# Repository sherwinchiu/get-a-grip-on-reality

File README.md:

# get-a-grip-on-reality
fydp project 2025 for vr gloves. open source pcb

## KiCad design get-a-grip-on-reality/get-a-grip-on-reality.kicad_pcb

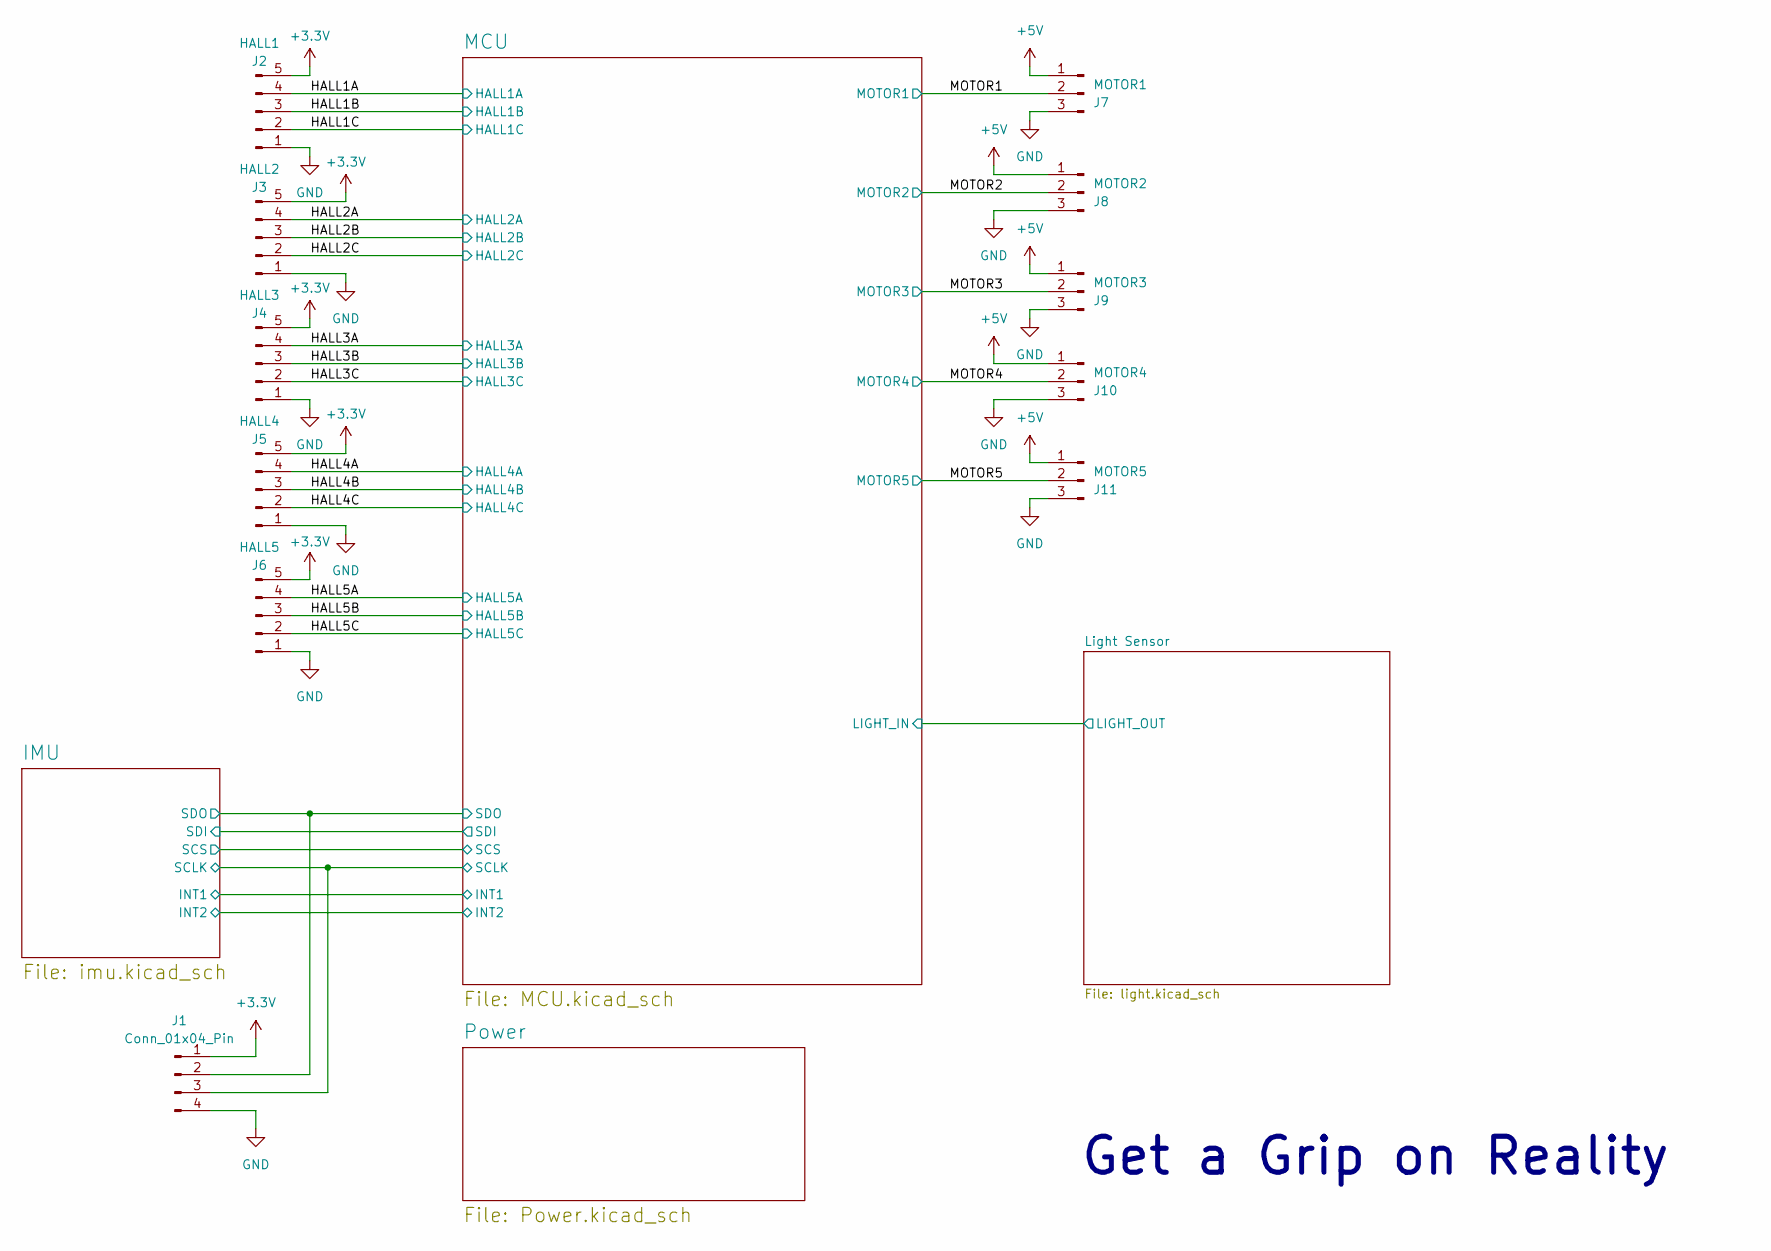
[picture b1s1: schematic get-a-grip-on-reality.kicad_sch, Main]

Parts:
J1: Conn_01x04_Pin; PinHeader_1x04_P2.54mm_Vertical
J2: HALL1; JST_SH_BM05B-SRSS-TB_1x05-1MP_P1.00mm_Vertical
J3: HALL2; JST_SH_BM05B-SRSS-TB_1x05-1MP_P1.00mm_Vertical
J4: HALL3; JST_SH_BM05B-SRSS-TB_1x05-1MP_P1.00mm_Vertical
J5: HALL4; JST_SH_BM05B-SRSS-TB_1x05-1MP_P1.00mm_Vertical
J6: HALL5; JST_SH_BM05B-SRSS-TB_1x05-1MP_P1.00mm_Vertical
J7: MOTOR1; PinHeader_1x03_P2.54mm_Vertical
J8: MOTOR2; PinHeader_1x03_P2.54mm_Vertical
J9: MOTOR3; PinHeader_1x03_P2.54mm_Vertical
J10: MOTOR4; PinHeader_1x03_P2.54mm_Vertical
J11: MOTOR5; PinHeader_1x03_P2.54mm_Vertical

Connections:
+3.3V: J1.1, J2.5, J3.5, J4.5, J5.5, J6.5; also elsewhere on the board
+5V: J7.1, J8.1, J9.1, J10.1, J11.1; also elsewhere on the board
/HALL1A: J2.4; also elsewhere on the board
/HALL1B: J2.3; also elsewhere on the board
/HALL1C: J2.2; also elsewhere on the board
/HALL2A: J3.4; also elsewhere on the board
/HALL2B: J3.3; also elsewhere on the board
/HALL2C: J3.2; also elsewhere on the board
/HALL3A: J4.4; also elsewhere on the board
/HALL3B: J4.3; also elsewhere on the board
/HALL3C: J4.2; also elsewhere on the board
/HALL4A: J5.4; also elsewhere on the board
/HALL4B: J5.3; also elsewhere on the board
/HALL4C: J5.2; also elsewhere on the board
/HALL5A: J6.4; also elsewhere on the board
/HALL5B: J6.3; also elsewhere on the board
/HALL5C: J6.2; also elsewhere on the board
/IMU/SCLK: J1.3; also elsewhere on the board
/IMU/SDO: J1.2; also elsewhere on the board
/MOTOR1: J7.2; also elsewhere on the board
/MOTOR2: J8.2; also elsewhere on the board
/MOTOR3: J9.2; also elsewhere on the board
/MOTOR4: J10.2; also elsewhere on the board
/MOTOR5: J11.2; also elsewhere on the board
GND: J1.4, J2.1, J3.1, J4.1, J5.1, J6.1, J7.3, J8.3, J9.3, J10.3, J11.3; also elsewhere on the board

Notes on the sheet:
Get a Grip on Reality

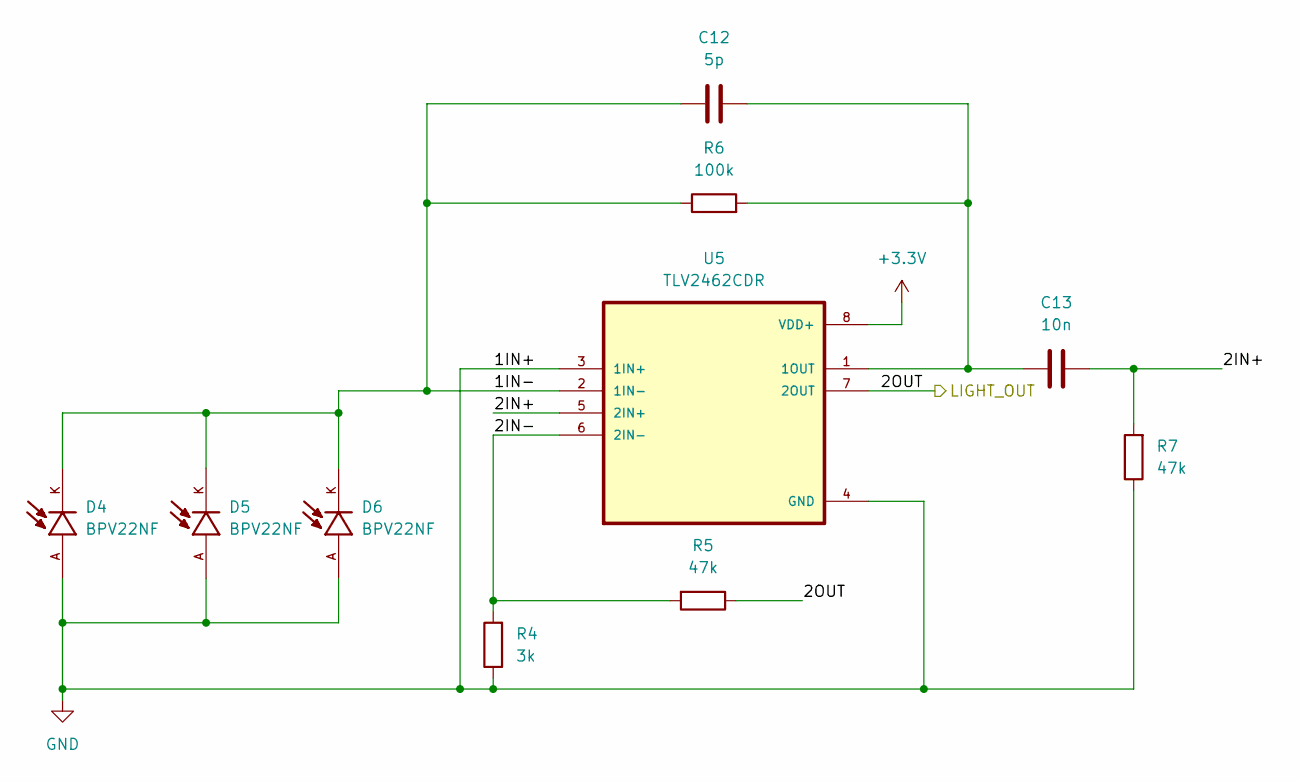
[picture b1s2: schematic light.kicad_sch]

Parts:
C12: 5p; C_0805_2012Metric
C13: 10n; C_0805_2012Metric
D4, D5, D6: BPV22NF; XDCR_BPV22NF; PARTREV 1.9
R4: 3k; R_0805_2012Metric
R5, R7: 47k; R_0805_2012Metric
R6: 100k; R_0805_2012Metric
U5: TLV2462CDR; SOIC127P599X175-8N

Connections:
+3.3V: U5.8 (VDD+); also elsewhere on the board
/Light Sensor/1IN-: C12.1, D4.K, D5.K, D6.K, R6.1, U5.2 (1IN-)
/Light Sensor/2IN+: C13.2, R7.2, U5.5 (2IN+)
/Light Sensor/2IN-: R4.2, R5.2, U5.6 (2IN-)
/Light Sensor/2OUT: R5.1, U5.7 (2OUT); also elsewhere on the board
GND: D4.A, D5.A, D6.A, R4.1, R7.1, U5.3 (1IN+), U5.4 (GND); also elsewhere on the board
unnamed: C12.2, C13.1, R6.2, U5.1 (1OUT)

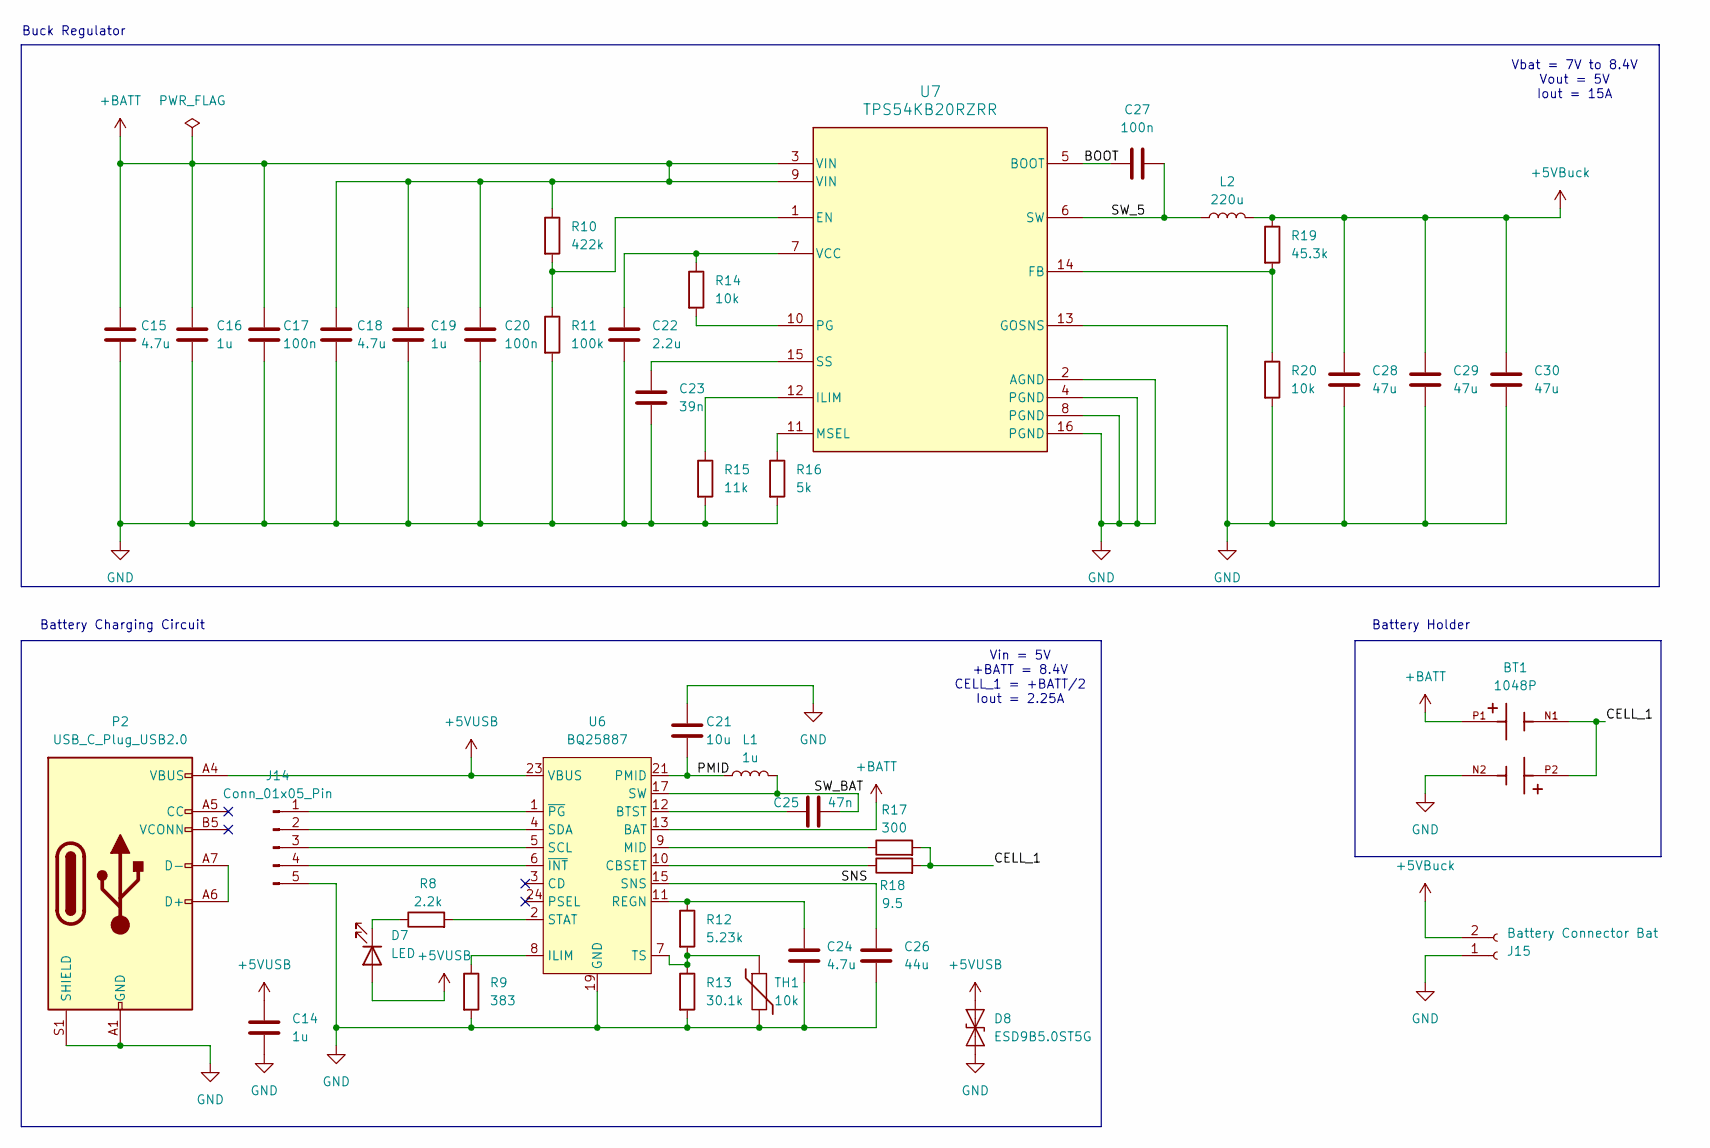
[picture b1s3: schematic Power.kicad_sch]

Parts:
BT1: 1048P; BAT_1048P; PARTREV A
C14, C16, C19: 1u; C_0805_2012Metric
C15, C18, C24: 4.7u; C_0805_2012Metric
C17, C20, C27: 100n; C_0805_2012Metric
C21: 10u; C_0805_2012Metric
C22: 2.2u; C_0805_2012Metric
C23: 39n; C_0805_2012Metric
C25: 47n; C_0805_2012Metric
C26: 44u; C_0805_2012Metric
C28, C29, C30: 47u; C_0805_2012Metric
D7: LED; LED_0805_2012Metric
D8: ESD9B5.0ST5G; D_SOD-923
J14: Conn_01x05_Pin; PinHeader_1x05_P2.54mm_Vertical
J15: Battery Connector Bat; AMASS_XT30PW-F_1x02_P2.50mm_Horizontal
L1: 1u; L_Taiyo-Yuden_MD-2020
L2: 220u; L_Bourns_SRU5016_5.2x5.2mm
P2: USB_C_Plug_USB2.0; USB_C_Receptacle_GCT_USB4110
R8: 2.2k; R_0805_2012Metric
R9: 383; R_0805_2012Metric
R10: 422k; R_0805_2012Metric
R11: 100k; R_0805_2012Metric
R12: 5.23k; R_0805_2012Metric
R13: 30.1k; R_0805_2012Metric
R14, R20: 10k; R_0805_2012Metric
R15: 11k; R_0805_2012Metric
R16: 5k; R_0805_2012Metric
R17: 300; R_0805_2012Metric
R18: 9.5; R_0805_2012Metric
R19: 45.3k; R_0805_2012Metric
TH1: 10k; R_0805_2012Metric
U6: BQ25887; VQFN-24-1EP_4x4mm_P0.5mm_EP2.5x2.5mm
U7: TPS54KB20RZRR; RZR0016A-MFG

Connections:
+5VBuck: C28.1, C29.1, C30.1, J15.2, L2.2, R19.1
+5VUSB: C14.1, D7.2 (A), D8.2 (A2), P2.A4 (VBUS), P2.A9 (VBUS), P2.B4 (VBUS), P2.B9 (VBUS), U6.23 (VBUS)
+BATT: BT1.P1, C15.1, C16.1, C17.1, C18.1, C19.1, C20.1, R10.1, U6.13 (BAT), U6.14 (BAT), U7.3 (VIN), U7.9 (VIN)
/Power/BOOT: C27.1, U7.5 (BOOT)
/Power/CELL_1: BT1.N1, BT1.P2, R17.2, R18.2
/Power/PMID: C21.2, L1.1, U6.21 (PMID), U6.22 (PMID)
/Power/SNS: C26.1, U6.15 (SNS), U6.16 (SNS)
/Power/SW_5: C27.2, L2.1, U7.6 (SW)
/Power/SW_BAT: C25.2, L1.2, U6.17 (SW), U6.18 (SW)
GND: BT1.N2, C14.2, C15.2, C16.2, C17.2, C18.2, C19.2, C20.2, C21.1, C22.2, C23.2, C24.2, C26.2, C28.2, C29.2, C30.2, D8.1 (A1), J14.5, J15.1, P2.A1 (GND), P2.A12 (GND), P2.B1 (GND), P2.B12 (GND), P2.S1 (SHIELD), R9.2, R11.2, R13.2, R15.2, R16.2, R20.2, TH1.2, U6.19 (GND), U6.20 (GND), U7.2 (AGND), U7.4 (PGND), U7.8 (PGND), U7.13 (GOSNS), U7.16 (PGND); also elsewhere on the board
unnamed: D7.1 (K), R8.1
unnamed: J14.1, U6.1 (~PG)
unnamed: J14.2, U6.4 (SDA)
unnamed: J14.3, U6.5 (SCL)
unnamed: J14.4, U6.6 (~INT)
unnamed: P2.A6 (D+), P2.A7 (D-)
unnamed: C25.1, U6.12 (BTST)
unnamed: R18.1, U6.10 (CBSET)
unnamed: R9.1, U6.8 (ILIM)
unnamed: R17.1, U6.9 (MID)
unnamed: C24.1, R12.1, U6.11 (REGN)
unnamed: R8.2, U6.2 (STAT)
unnamed: R12.2, R13.1, TH1.1, U6.7 (TS)
unnamed: R10.2, R11.1, U7.1 (EN)
unnamed: R19.2, R20.1, U7.14 (FB)
unnamed: R15.1, U7.12 (ILIM)
unnamed: R16.1, U7.11 (MSEL)
unnamed: R14.2, U7.10 (PG)
unnamed: C23.1, U7.15 (SS)
unnamed: C22.1, R14.1, U7.7 (VCC)

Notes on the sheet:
Vbat = 7V to 8.4V Vout = 5V Iout = 15A
Buck Regulator
Vin = 5V +BATT = 8.4V CELL_1 = +BATT/2 Iout = 2.25A
Battery Charging Circuit
Battery Holder

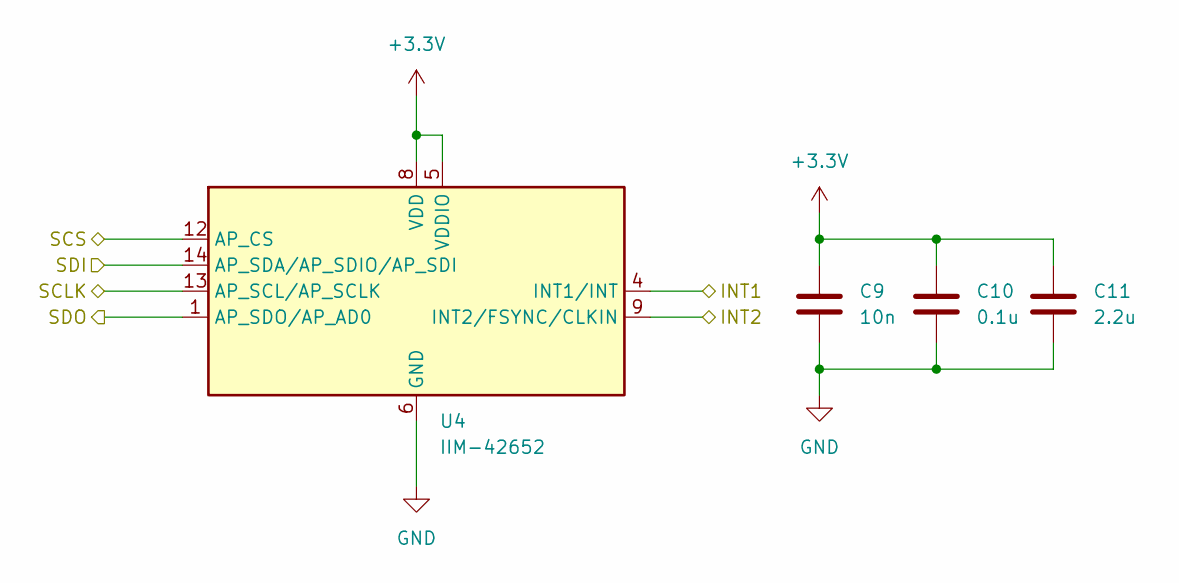
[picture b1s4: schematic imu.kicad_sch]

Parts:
C9: 10n; C_0805_2012Metric
C10: 0.1u; C_0805_2012Metric
C11: 2.2u; C_0805_2012Metric
U4: IIM-42652; Bosch_LGA-14_3x2.5mm_P0.5mm

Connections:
+3.3V: C9.1, C10.1, C11.1, U4.5 (VDDIO), U4.8 (VDD); also elsewhere on the board
/IMU/INT1: U4.4 (INT1/INT); also elsewhere on the board
/IMU/INT2: U4.9 (INT2/FSYNC/CLKIN); also elsewhere on the board
/IMU/SCLK: U4.13 (AP_SCL/AP_SCLK); also elsewhere on the board
/IMU/SCS: U4.12 (AP_CS); also elsewhere on the board
/IMU/SDI: U4.14 (AP_SDA/AP_SDIO/AP_SDI); also elsewhere on the board
/IMU/SDO: U4.1 (AP_SDO/AP_AD0); also elsewhere on the board
GND: C9.2, C10.2, C11.2, U4.6 (GND), U4.7 (GND); also elsewhere on the board

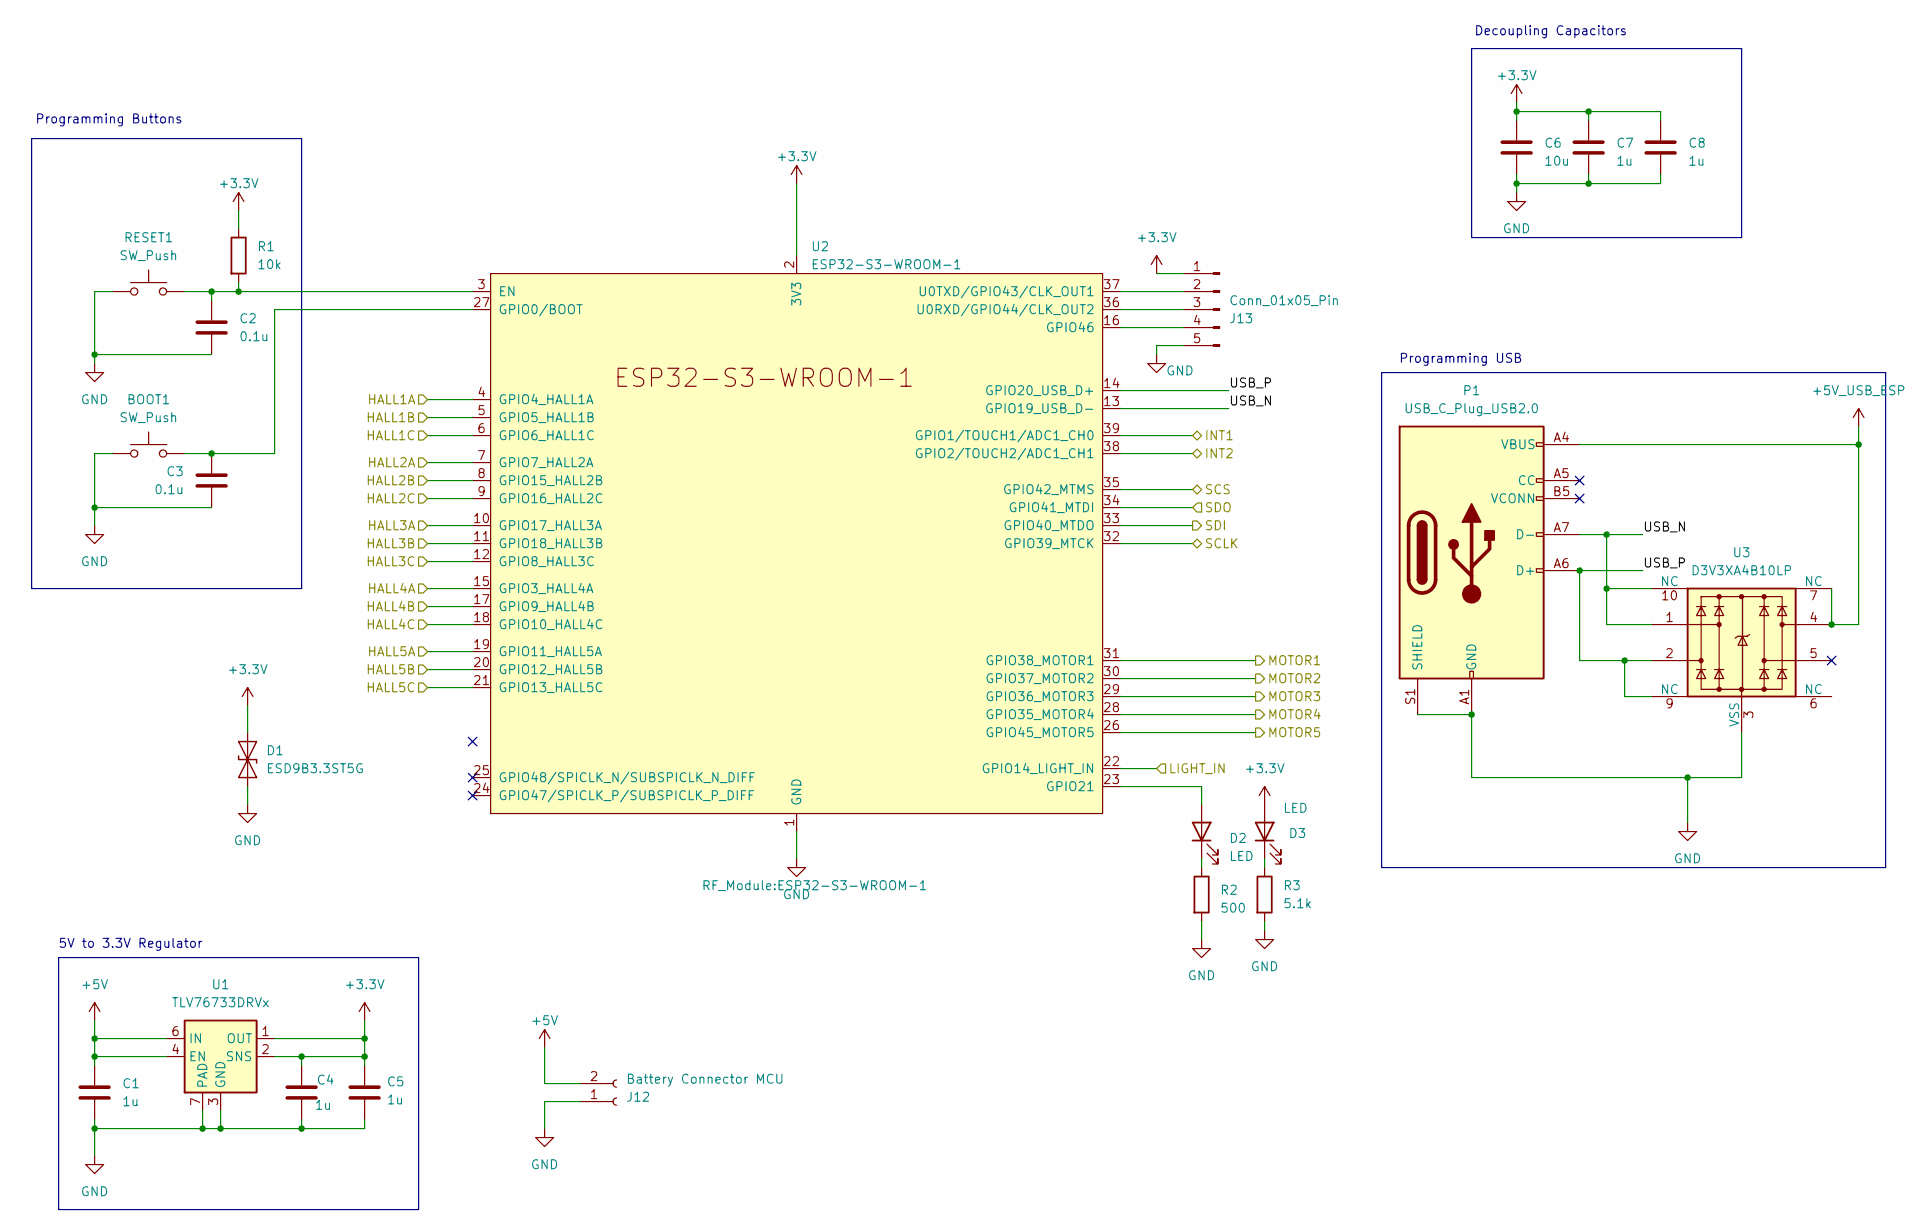
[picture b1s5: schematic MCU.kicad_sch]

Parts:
BOOT1: SW_Push; SW_SPST_EVPBF
C1, C4, C5, C7, C8: 1u; C_0805_2012Metric
C2, C3: 0.1u; C_0805_2012Metric
C6: 10u; C_0805_2012Metric
D1: ESD9B3.3ST5G; D_SOD-923
D2, D3: LED; LED_0805_2012Metric
J12: Battery Connector MCU; AMASS_XT30PW-M_1x02_P2.50mm_Horizontal
J13: Conn_01x05_Pin; PinHeader_1x05_P2.54mm_Vertical
P1: USB_C_Plug_USB2.0; USB_C_Receptacle_GCT_USB4110
R1: 10k; R_0805_2012Metric
R2: 500; R_0805_2012Metric
R3: 5.1k; R_0805_2012Metric
RESET1: SW_Push; SW_SPST_EVPBF
U1: TLV76733DRVx; WSON-6-1EP_2x2mm_P0.65mm_EP1x1.6mm_ThermalVias
U2: ESP32-S3-WROOM-1
U3: D3V3XA4B10LP; Diodes_UDFN-10_1.0x2.5mm_P0.5mm

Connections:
+3.3V: C4.1, C5.1, C6.1, C7.1, C8.1, D1.2 (A2), D3.2 (A), J13.1, R1.1, U1.1 (OUT), U1.2 (SNS), U2.2 (3V3); also elsewhere on the board
+5V: C1.1, J12.2, U1.4 (EN), U1.6 (IN); also elsewhere on the board
+5V_USB_ESP: P1.A4 (VBUS), P1.A9 (VBUS), P1.B4 (VBUS), P1.B9 (VBUS), U3.4, U3.7 (NC)
/HALL1A: U2.4 (GPIO4_HALL1A); also elsewhere on the board
/HALL1B: U2.5 (GPIO5_HALL1B); also elsewhere on the board
/HALL1C: U2.6 (GPIO6_HALL1C); also elsewhere on the board
/HALL2A: U2.7 (GPIO7_HALL2A); also elsewhere on the board
/HALL2B: U2.8 (GPIO15_HALL2B); also elsewhere on the board
/HALL2C: U2.9 (GPIO16_HALL2C); also elsewhere on the board
/HALL3A: U2.10 (GPIO17_HALL3A); also elsewhere on the board
/HALL3B: U2.11 (GPIO18_HALL3B); also elsewhere on the board
/HALL3C: U2.12 (GPIO8_HALL3C); also elsewhere on the board
/HALL4A: U2.15 (GPIO3_HALL4A); also elsewhere on the board
/HALL4B: U2.17 (GPIO9_HALL4B); also elsewhere on the board
/HALL4C: U2.18 (GPIO10_HALL4C); also elsewhere on the board
/HALL5A: U2.19 (GPIO11_HALL5A); also elsewhere on the board
/HALL5B: U2.20 (GPIO12_HALL5B); also elsewhere on the board
/HALL5C: U2.21 (GPIO13_HALL5C); also elsewhere on the board
/IMU/INT1: U2.39 (GPIO1/TOUCH1/ADC1_CH0); also elsewhere on the board
/IMU/INT2: U2.38 (GPIO2/TOUCH2/ADC1_CH1); also elsewhere on the board
/IMU/SCLK: U2.32 (GPIO39_MTCK); also elsewhere on the board
/IMU/SCS: U2.35 (GPIO42_MTMS); also elsewhere on the board
/IMU/SDI: U2.33 (GPIO40_MTDO); also elsewhere on the board
/IMU/SDO: U2.34 (GPIO41_MTDI); also elsewhere on the board
/Light Sensor/2OUT: U2.22 (GPIO14_LIGHT_IN); also elsewhere on the board
/MCU/USB_N: P1.A7 (D-), U2.13 (GPIO19_USB_D-), U3.1, U3.10 (NC)
/MCU/USB_P: P1.A6 (D+), U2.14 (GPIO20_USB_D+), U3.2, U3.9 (NC)
/MOTOR1: U2.31 (GPIO38_MOTOR1); also elsewhere on the board
/MOTOR2: U2.30 (GPIO37_MOTOR2); also elsewhere on the board
/MOTOR3: U2.29 (GPIO36_MOTOR3); also elsewhere on the board
/MOTOR4: U2.28 (GPIO35_MOTOR4); also elsewhere on the board
/MOTOR5: U2.26 (GPIO45_MOTOR5); also elsewhere on the board
GND: BOOT1.2, C1.2, C2.2, C3.2, C4.2, C5.2, C6.2, C7.2, C8.2, D1.1 (A1), J12.1, J13.5, P1.A1 (GND), P1.A12 (GND), P1.B1 (GND), P1.B12 (GND), P1.S1 (SHIELD), R2.2, R3.2, RESET1.1, U1.3 (GND), U1.5 (GND), U1.7 (PAD), U2.1 (GND), U2.40 (GND), U2.41 (GND), U3.3 (VSS), U3.8 (VSS); also elsewhere on the board
unnamed: D2.2 (A), U2.23 (GPIO21)
unnamed: D2.1 (K), R2.1
unnamed: D3.1 (K), R3.1
unnamed: J13.2, U2.37 (U0TXD/GPIO43/CLK_OUT1)
unnamed: J13.3, U2.36 (U0RXD/GPIO44/CLK_OUT2)
unnamed: J13.4, U2.16 (GPIO46)
unnamed: C2.1, R1.2, RESET1.2, U2.3 (EN)
unnamed: BOOT1.1, C3.1, U2.27 (GPIO0/BOOT)

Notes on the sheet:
Programming Buttons
5V to 3.3V Regulator
Decoupling Capacitors
Programming USB

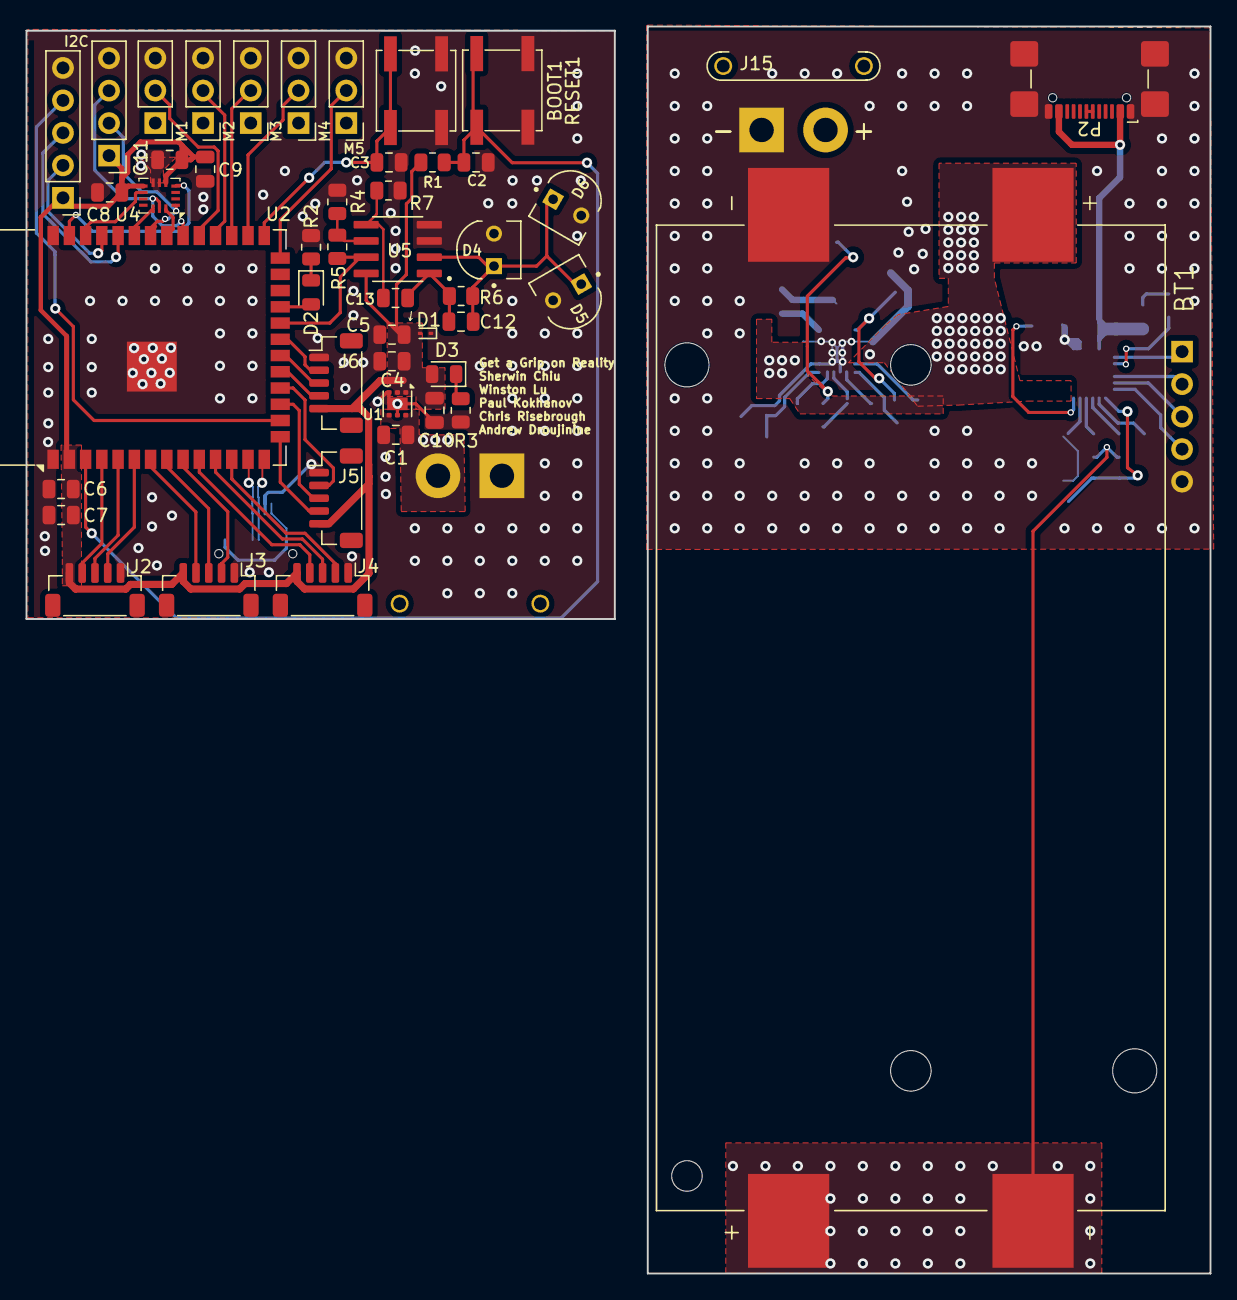
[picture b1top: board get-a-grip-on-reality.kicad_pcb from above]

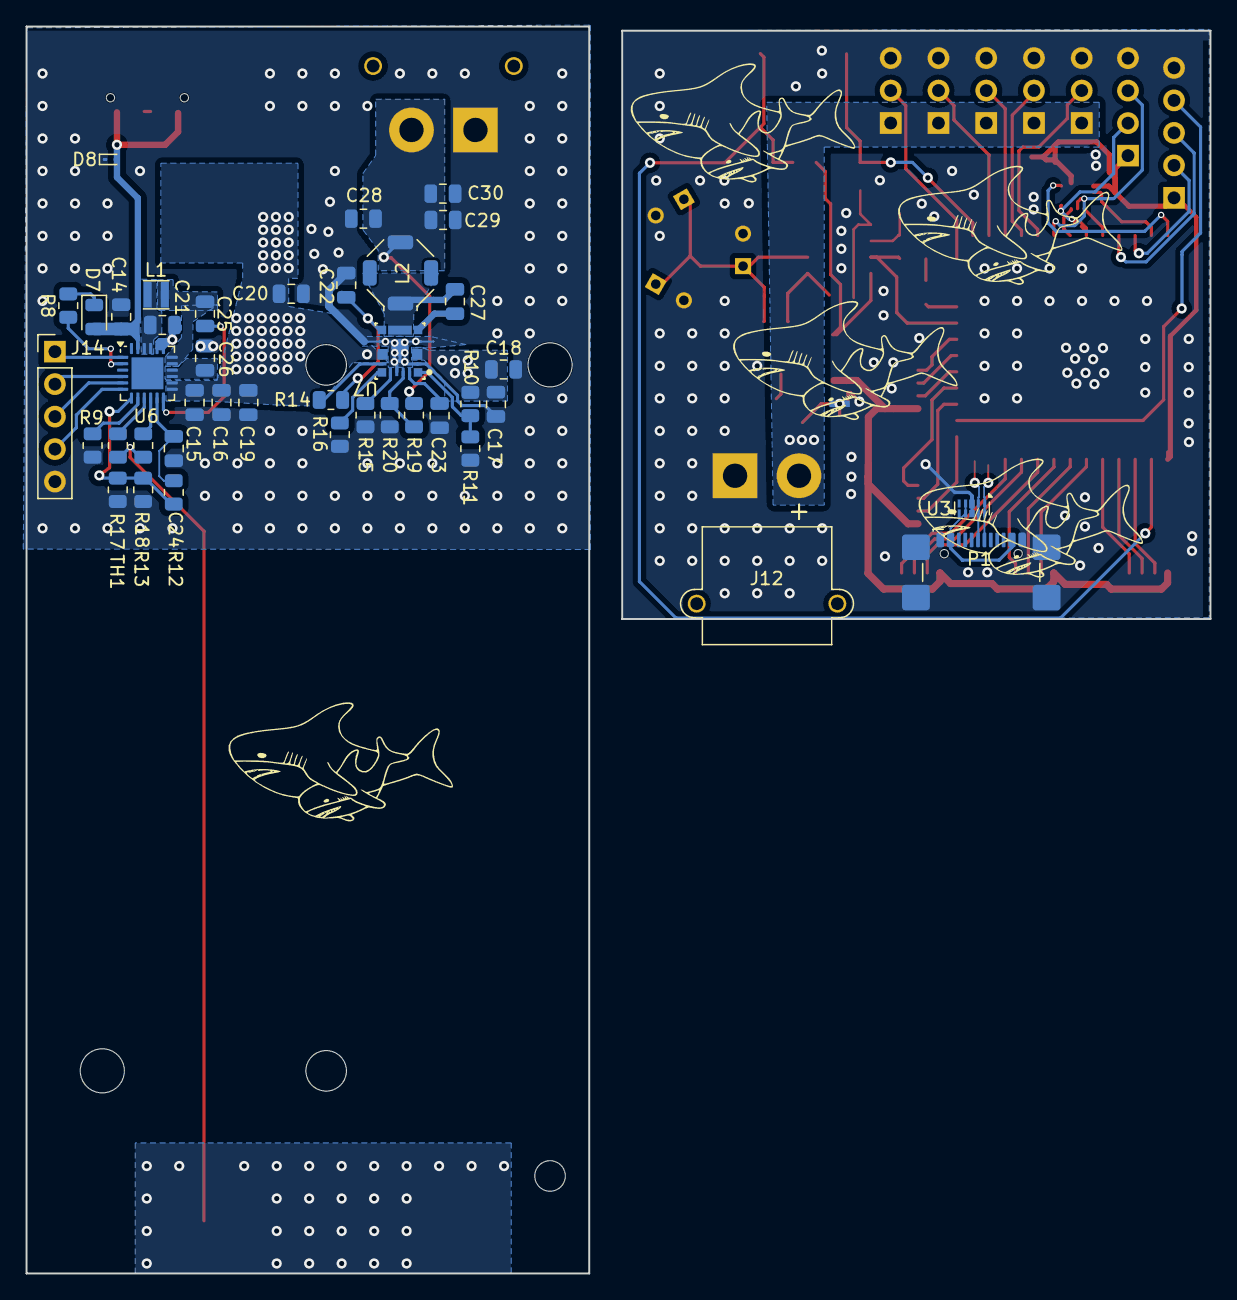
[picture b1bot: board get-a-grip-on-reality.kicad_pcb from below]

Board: 2 copper layers, 92.6 x 97.5 mm, 93 parts (46 on the bottom side), 74 nets.

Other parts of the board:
 : LOGO; logo_shark
 #2,  #3,  #4,  #5: LOGO; logo_shark

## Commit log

2024-06-14 add hierachal sheets
2024-06-14 add bq25170
2024-06-14 move component slightly
2024-06-15 power wip
2024-06-15 add mcu schematic
2024-06-15 power out
2024-06-15 power
2024-06-15 my changes
2024-06-25 add new chips
2024-06-26 finish mcu and power page
2024-06-27 add output
2024-06-28 add more to pcb
2024-07-10 fix schematic with winstons suggestions
2024-07-10 finish top pcb
2024-07-11 added review comments
2024-07-12 add pdb
2024-07-13 finish pcb no drc errors
2024-07-13 put designators in proper places
2024-07-13 add final changes + gerbers
2024-07-13 more comments
2024-07-14 implement all of winstons comments
2024-07-14 add more changes
2024-07-15 fixes to pcb
2024-07-15 add more shorks
2024-07-16 add edge marks separately for pcbs
2024-07-16 final version
2024-11-01 add test.ino for ble and imu test
2024-11-02 ble and other stuff
2025-01-24 hall sensor code
2025-02-08 add calibration code
2025-02-09 commit working code
2025-02-09 things changed
2025-02-13 uncommit logger code
2025-02-14 fixed transmit
2025-02-24 servo and most things workey
2025-03-03 working firmware
2026-06-15 add mobile demo and rtos version of glove, improve schematic
2026-06-19 change glove firmware
2026-06-19 change to have working rtos code
2026-06-20 add imu
2026-06-20 bluetooth
